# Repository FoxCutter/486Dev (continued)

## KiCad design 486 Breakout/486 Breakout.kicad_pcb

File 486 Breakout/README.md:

# 486 Breakout Board

## SMD parts

The decoupling capacitors for the CPU are made with surface mount parts. This is done because the gap the socket provides between board and CPU is fairly limited, and while Through-Hole parts can be used, they might not have enough clearance. Now these are using 0805/2012 size resistors, and are fairly spread out so there should be enough room even if you've never worked with surface mount parts before.

The capacitors themselves are 1uF (marked as 105), and are fairly inexpensive.

## 7400 ICs

The pair of 7400 NAND gate ICs provide the logic for generating the _BHE#_, _BHL#_, _A1_ and _A0_ and can be left off the board if you do not need or would rather generate those signals yourself.

## CPU Socket

The components on the board and spaced such that a standard ZIF socket should fit correctly. This is not a guarantee, but it should work.

Otherwise, a 17x17 PGA socket (168 or 169 pin) should be used.

## _DP0_-_DP3_

These are the data parity lines for each byte in the data bus. The spec sheet advises that if you are not using them to pull them high. This is what the **J2** jumper block is for.

These lines have no effect other then on the output of the _PCHK#_ pin.

## _RDY#_ and _BRDY#_ jumpers

Jumper block **J10** exists as a way to set the _RDY#_ and _BRDY#_ pins if you don't plan to dynamically set them. The recommended configuration is to pull _RDY#_ low, to indicate that the normal data bus access as complete, and _BRDY#_ to high to disable burst access.

Both High and Low will go through a pull-up resistor, so can be overridden by other parts of the system.

## _IGNNE#_, _KEN#_ and _A20M#_ jumpers

Jumper block **J6** allows you to force any of these three lines to low, as all three are pulled high on the board. _IGNNE#_ is ignored if the NE bit is set in CR0 (which you should do), and the _A20M#_ is the state of the A20 Line mask, and is not very useful unless you are making an IBM PC compatible system.

NOTE: This jumper is the only place where the _A20M#_ line is exposed on the breakout board.

The _KEN#_ line indicates the cachability of the current cycle. And probably isn't worth asserting the line to ground.

## Other Versions of the 486

The breakout board is built around the 486-DX that I own, it should be usable with a later version of the DX chip. Though in that case some of the previously not connected pins will now be connected.

Make sure you cross reference the extra pins against the correct data-sheet for your CPU. I'm hardly an expert and the advice below could turn out to be wrong.

### 486-SX

The original version of the 486SX has a slightly different pin arrangement, and while it should work if you are careful, I wouldn't recommend it. There should be no risk of damaging the CPU, but it might not function as expected.

### Later version of the 486-DX

Later version of the DX add a few new pins, _SRESET_, _SMI#_, _SMIACT#_, _STPCLK#_ and _UP#_. While these have built in pull up/down resisters, if the cpu you are working on has them, it would be best to pull _SRESET_ low, and _SMI#_, _STPCLK#_ and _UP#_ high.

### 486-DX2 And 486-SX2

The biggest change for the DX2 is that the internal clock speed is doubled. It doesn't seem to add any additional pins outside of what was already added above.

The SX2 brought the pins in line with the DX2, so should be fully compatible.

### 486-DX4

The DX4 adds the ability to control the clock multiplier using the **CLKMUL** pin durring a reset. So you need to make sure that the pin is properly pulled up/down depending on how you want to use the multiplier. 

In addititon, the DX4 is a 3 volt CPU.

### 3 Volt CPU

This is probably the most challenging chip to work with, as it runs at 3.3 volts and not 5 volts. It can support 5v logic, but extra steps are needed to provide a 5 volt reference input to the _J1_ pin on the cpu.

Please double check the data sheet before doing this, to make sure things work the way you will want them to!

If you are using the 3.3 volt cpu with 5 volt logic, you must cut jumper **JP1** on the back of the board, and attach a 5 volt input to **TP1**. Failing to do this could cause undefined results.

### Test Port

The test port is available on some DX models, and appears to be on all DX3 and DX4 chips. This adds the _TCK_, _TDI_, _TMS_ and _TDO_ pins. The test port pins are allowed to be unconnected on some versions of the DX and DX2, but it's probably wise to pull the input lines (_TCK_, _TDI_ and _TMS_) high unless you plan on using it.

### Write-Back Enhanced

The Write-Back Enhanced version of the DX2 and DX4 add the _INV_, _HITM#_, _CHACH#_ and _WB-WT#_ pins. The _INV_ pin should be pulled high, while the _FLUSH#_ pin should be pulled low.

### Can I use the 486 Symbol/Footprint in my own projects?

Of course, they are standard Kicad Symbols and Footprint, and you can ues them without credit. I tried to make them as generic as possible for all PGA versions of the DX and majority of SX cpus (the same issues with the SX from above apply). You would need to adjust and add some pins for the QFP versions.

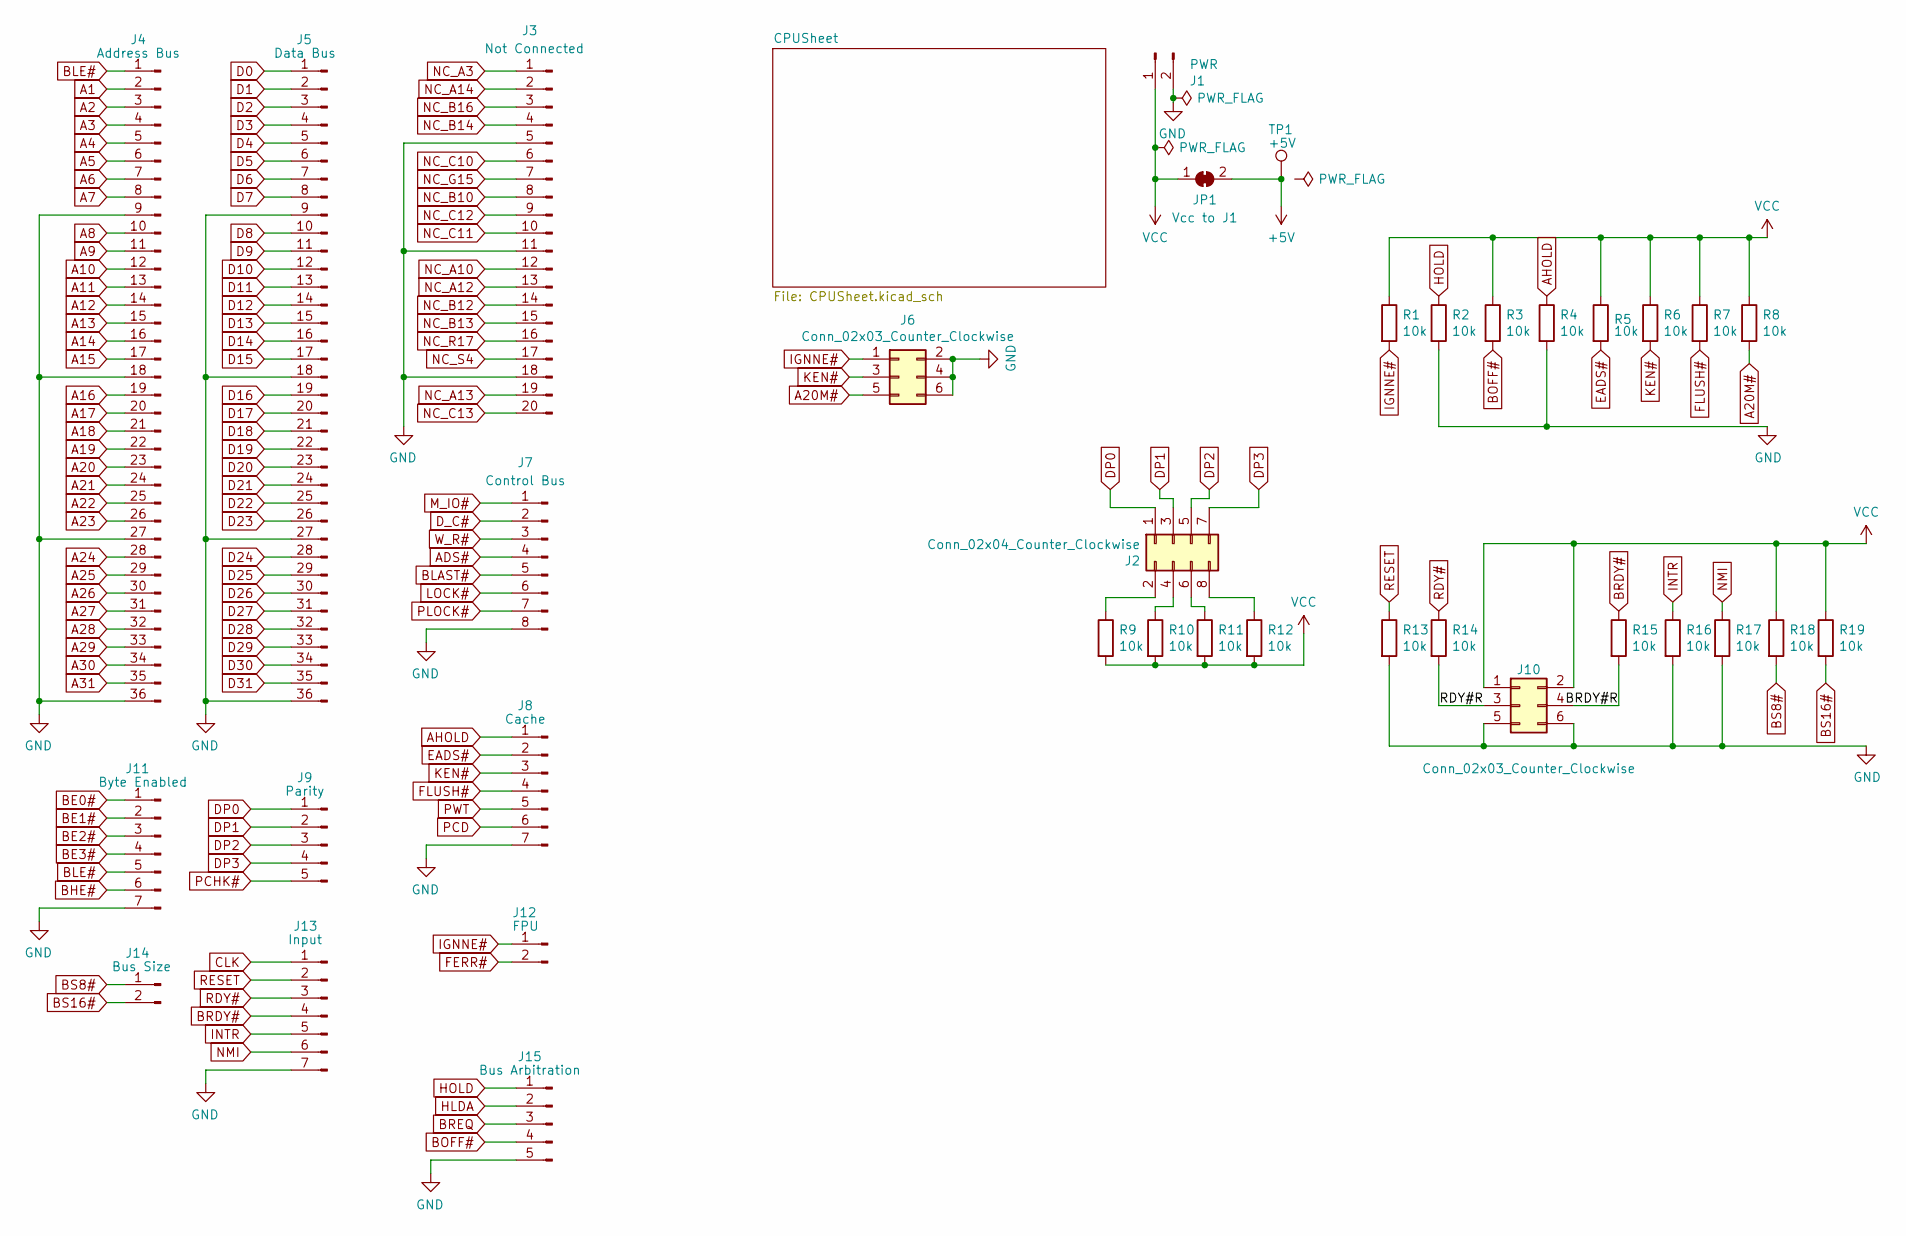
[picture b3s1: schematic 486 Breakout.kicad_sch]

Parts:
J1: PWR; PinHeader_1x02_P2.54mm_Vertical
J2: Conn_02x04_Counter_Clockwise; PinHeader_2x04_P2.54mm_Vertical
J3: Not Connected; PinHeader_1x20_P2.54mm_Vertical
J4: Address Bus; PinHeader_1x36_P2.54mm_Vertical
J5: Data Bus; PinHeader_1x36_P2.54mm_Vertical
J6, J10: Conn_02x03_Counter_Clockwise; PinHeader_2x03_P2.54mm_Vertical
J7: Control Bus; PinHeader_1x08_P2.54mm_Vertical
J8: Cache; PinHeader_1x07_P2.54mm_Vertical
J9: Parity; PinHeader_1x05_P2.54mm_Vertical
J11: Byte Enabled; PinHeader_1x07_P2.54mm_Vertical
J12: FPU; PinHeader_1x02_P2.54mm_Vertical
J13: Input; PinHeader_1x07_P2.54mm_Vertical
J14: Bus Size; PinHeader_1x02_P2.54mm_Vertical
J15: Bus Arbitration; PinHeader_1x05_P2.54mm_Vertical
JP1: Vcc to J1; SolderJumper-2_P1.3mm_Bridged_Pad1.0x1.5mm
R1, R2, R3, R4, R5, R6, R7, R8, R9, R10, R11, R12, R13, R14, R15, R16, R17, R18, R19: 10k; R_Axial_DIN0204_L3.6mm_D1.6mm_P7.62mm_Horizontal
TP1: +5V; TestPoint_Pad_2.0x2.0mm

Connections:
+5V: JP1.2 (B), TP1.1; also elsewhere on the board
/BRDY#R: J10.4, R15.2
/RDY#R: J10.3, R14.2
A1: J4.2; also elsewhere on the board
A2: J4.3; also elsewhere on the board
A3: J4.4; also elsewhere on the board
A4: J4.5; also elsewhere on the board
A5: J4.6; also elsewhere on the board
A6: J4.7; also elsewhere on the board
A7: J4.8; also elsewhere on the board
A8: J4.10; also elsewhere on the board
A9: J4.11; also elsewhere on the board
A10: J4.12; also elsewhere on the board
A11: J4.13; also elsewhere on the board
A12: J4.14; also elsewhere on the board
A13: J4.15; also elsewhere on the board
A14: J4.16; also elsewhere on the board
A15: J4.17; also elsewhere on the board
A16: J4.19; also elsewhere on the board
A17: J4.20; also elsewhere on the board
A18: J4.21; also elsewhere on the board
A19: J4.22; also elsewhere on the board
A20: J4.23; also elsewhere on the board
A20M#: J6.5, R8.2; also elsewhere on the board
A21: J4.24; also elsewhere on the board
A22: J4.25; also elsewhere on the board
A23: J4.26; also elsewhere on the board
A24: J4.28; also elsewhere on the board
A25: J4.29; also elsewhere on the board
A26: J4.30; also elsewhere on the board
A27: J4.31; also elsewhere on the board
A28: J4.32; also elsewhere on the board
A29: J4.33; also elsewhere on the board
A30: J4.34; also elsewhere on the board
A31: J4.35; also elsewhere on the board
ADS#: J7.4; also elsewhere on the board
AHOLD: J8.1, R4.1; also elsewhere on the board
BE0#: J11.1; also elsewhere on the board
BE1#: J11.2; also elsewhere on the board
BE2#: J11.3; also elsewhere on the board
BE3#: J11.4; also elsewhere on the board
BHE#: J11.6; also elsewhere on the board
BLAST#: J7.5; also elsewhere on the board
BLE#: J4.1, J11.5; also elsewhere on the board
BOFF#: J15.4, R3.2; also elsewhere on the board
BRDY#: J13.4, R15.1; also elsewhere on the board
BREQ: J15.3; also elsewhere on the board
BS8#: J14.1, R18.2; also elsewhere on the board
BS16#: J14.2, R19.2; also elsewhere on the board
CLK: J13.1; also elsewhere on the board
D0: J5.1; also elsewhere on the board
D1: J5.2; also elsewhere on the board
D2: J5.3; also elsewhere on the board
D3: J5.4; also elsewhere on the board
D4: J5.5; also elsewhere on the board
D5: J5.6; also elsewhere on the board
D6: J5.7; also elsewhere on the board
D7: J5.8; also elsewhere on the board
D8: J5.10; also elsewhere on the board
D9: J5.11; also elsewhere on the board
D10: J5.12; also elsewhere on the board
D11: J5.13; also elsewhere on the board
D12: J5.14; also elsewhere on the board
D13: J5.15; also elsewhere on the board
D14: J5.16; also elsewhere on the board
D15: J5.17; also elsewhere on the board
D16: J5.19; also elsewhere on the board
D17: J5.20; also elsewhere on the board
D18: J5.21; also elsewhere on the board
D19: J5.22; also elsewhere on the board
D20: J5.23; also elsewhere on the board
D21: J5.24; also elsewhere on the board
D22: J5.25; also elsewhere on the board
D23: J5.26; also elsewhere on the board
D24: J5.28; also elsewhere on the board
D25: J5.29; also elsewhere on the board
D26: J5.30; also elsewhere on the board
D27: J5.31; also elsewhere on the board
D28: J5.32; also elsewhere on the board
D29: J5.33; also elsewhere on the board
D30: J5.34; also elsewhere on the board
D31: J5.35; also elsewhere on the board
DP0: J2.1, J9.1; also elsewhere on the board
DP1: J2.3, J9.2; also elsewhere on the board
DP2: J2.5, J9.3; also elsewhere on the board
DP3: J2.7, J9.4; also elsewhere on the board
D_C#: J7.2; also elsewhere on the board
EADS#: J8.2, R5.2; also elsewhere on the board
FERR#: J12.2; also elsewhere on the board
FLUSH#: J8.4, R7.2; also elsewhere on the board
GND: J1.2, J3.5, J3.11, J3.18, J4.9, J4.18, J4.27, J4.36, J5.9, J5.18, J5.27, J5.36, J6.2, J6.4, J6.6, J7.8, J8.7, J10.5, J10.6, J11.7, J13.7, J15.5, R2.2, R4.2, R13.2, R16.2, R17.2; also elsewhere on the board
HLDA: J15.2; also elsewhere on the board
HOLD: J15.1, R2.1; also elsewhere on the board
IGNNE#: J6.1, J12.1, R1.2; also elsewhere on the board
INTR: J13.5, R16.1; also elsewhere on the board
KEN#: J6.3, J8.3, R6.2; also elsewhere on the board
LOCK#: J7.6; also elsewhere on the board
M_IO#: J7.1; also elsewhere on the board
NC_A3: J3.1; also elsewhere on the board
NC_A10: J3.12; also elsewhere on the board
NC_A12: J3.13; also elsewhere on the board
NC_A13: J3.19; also elsewhere on the board
NC_A14: J3.2; also elsewhere on the board
NC_B10: J3.8; also elsewhere on the board
NC_B12: J3.14; also elsewhere on the board
NC_B13: J3.15; also elsewhere on the board
NC_B14: J3.4; also elsewhere on the board
NC_B16: J3.3; also elsewhere on the board
NC_C10: J3.6; also elsewhere on the board
NC_C11: J3.10; also elsewhere on the board
NC_C12: J3.9; also elsewhere on the board
NC_C13: J3.20; also elsewhere on the board
NC_G15: J3.7; also elsewhere on the board
NC_R17: J3.16; also elsewhere on the board
NC_S4: J3.17; also elsewhere on the board
NMI: J13.6, R17.1; also elsewhere on the board
unnamed: J2.2, R9.1
unnamed: J2.4, R10.1
unnamed: J2.6, R11.1
unnamed: J2.8, R12.1
PCD: J8.6; also elsewhere on the board
PCHK#: J9.5; also elsewhere on the board
PLOCK#: J7.7; also elsewhere on the board
PWT: J8.5; also elsewhere on the board
RDY#: J13.3, R14.1; also elsewhere on the board
RESET: J13.2, R13.1; also elsewhere on the board
VCC: J1.1, J10.1, J10.2, JP1.1 (A), R1.1, R3.1, R5.1, R6.1, R7.1, R8.1, R9.2, R10.2, R11.2, R12.2, R18.1, R19.1; also elsewhere on the board
W_R#: J7.3; also elsewhere on the board

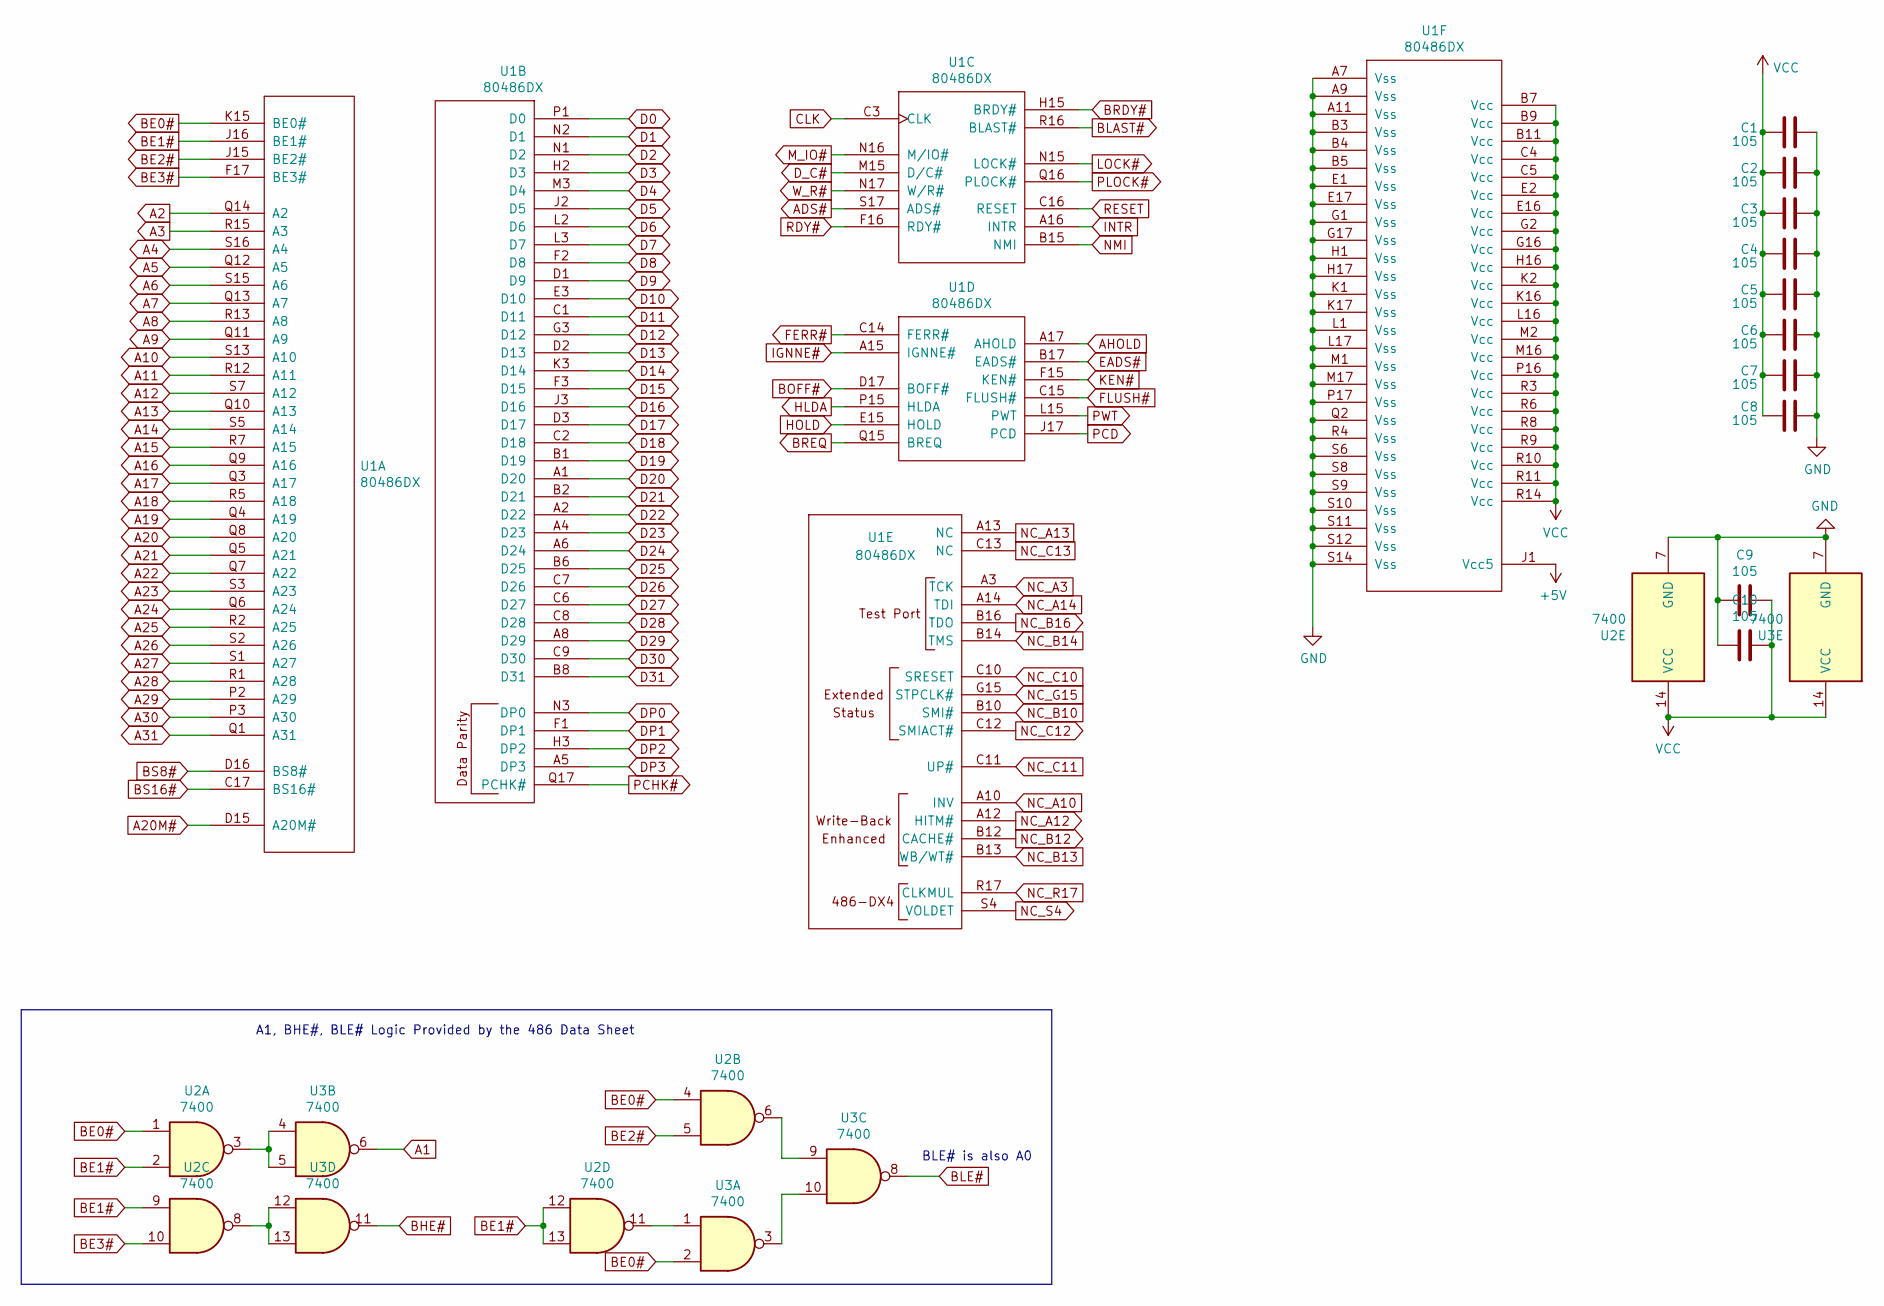
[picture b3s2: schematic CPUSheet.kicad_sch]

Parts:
C1, C2, C3, C4, C5, C6, C7, C8: 105; C_0805_2012Metric_Pad1.18x1.45mm_HandSolder
C9, C10: 105; C_Disc_D3.4mm_W2.1mm_P2.50mm
U1: 80486DX; PGA169
U2, U3: 7400; DIP-14_W7.62mm

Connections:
+5V: U1.J1 (Vcc5); also elsewhere on the board
A1: U3.6; also elsewhere on the board
A2: U1.Q14 (A2); also elsewhere on the board
A3: U1.R15 (A3); also elsewhere on the board
A4: U1.S16 (A4); also elsewhere on the board
A5: U1.Q12 (A5); also elsewhere on the board
A6: U1.S15 (A6); also elsewhere on the board
A7: U1.Q13 (A7); also elsewhere on the board
A8: U1.R13 (A8); also elsewhere on the board
A9: U1.Q11 (A9); also elsewhere on the board
A10: U1.S13 (A10); also elsewhere on the board
A11: U1.R12 (A11); also elsewhere on the board
A12: U1.S7 (A12); also elsewhere on the board
A13: U1.Q10 (A13); also elsewhere on the board
A14: U1.S5 (A14); also elsewhere on the board
A15: U1.R7 (A15); also elsewhere on the board
A16: U1.Q9 (A16); also elsewhere on the board
A17: U1.Q3 (A17); also elsewhere on the board
A18: U1.R5 (A18); also elsewhere on the board
A19: U1.Q4 (A19); also elsewhere on the board
A20: U1.Q8 (A20); also elsewhere on the board
A20M#: U1.D15 (A20M#); also elsewhere on the board
A21: U1.Q5 (A21); also elsewhere on the board
A22: U1.Q7 (A22); also elsewhere on the board
A23: U1.S3 (A23); also elsewhere on the board
A24: U1.Q6 (A24); also elsewhere on the board
A25: U1.R2 (A25); also elsewhere on the board
A26: U1.S2 (A26); also elsewhere on the board
A27: U1.S1 (A27); also elsewhere on the board
A28: U1.R1 (A28); also elsewhere on the board
A29: U1.P2 (A29); also elsewhere on the board
A30: U1.P3 (A30); also elsewhere on the board
A31: U1.Q1 (A31); also elsewhere on the board
ADS#: U1.S17 (ADS#); also elsewhere on the board
AHOLD: U1.A17 (AHOLD); also elsewhere on the board
BE0#: U1.K15 (BE0#), U2.1, U2.4, U3.2; also elsewhere on the board
BE1#: U1.J16 (BE1#), U2.2, U2.9, U2.12, U2.13; also elsewhere on the board
BE2#: U1.J15 (BE2#), U2.5; also elsewhere on the board
BE3#: U1.F17 (BE3#), U2.10; also elsewhere on the board
BHE#: U3.11; also elsewhere on the board
BLAST#: U1.R16 (BLAST#); also elsewhere on the board
BLE#: U3.8; also elsewhere on the board
BOFF#: U1.D17 (BOFF#); also elsewhere on the board
BRDY#: U1.H15 (BRDY#); also elsewhere on the board
BREQ: U1.Q15 (BREQ); also elsewhere on the board
BS8#: U1.D16 (BS8#); also elsewhere on the board
BS16#: U1.C17 (BS16#); also elsewhere on the board
CLK: U1.C3 (CLK); also elsewhere on the board
D0: U1.P1 (D0); also elsewhere on the board
D1: U1.N2 (D1); also elsewhere on the board
D2: U1.N1 (D2); also elsewhere on the board
D3: U1.H2 (D3); also elsewhere on the board
D4: U1.M3 (D4); also elsewhere on the board
D5: U1.J2 (D5); also elsewhere on the board
D6: U1.L2 (D6); also elsewhere on the board
D7: U1.L3 (D7); also elsewhere on the board
D8: U1.F2 (D8); also elsewhere on the board
D9: U1.D1 (D9); also elsewhere on the board
D10: U1.E3 (D10); also elsewhere on the board
D11: U1.C1 (D11); also elsewhere on the board
D12: U1.G3 (D12); also elsewhere on the board
D13: U1.D2 (D13); also elsewhere on the board
D14: U1.K3 (D14); also elsewhere on the board
D15: U1.F3 (D15); also elsewhere on the board
D16: U1.J3 (D16); also elsewhere on the board
D17: U1.D3 (D17); also elsewhere on the board
D18: U1.C2 (D18); also elsewhere on the board
D19: U1.B1 (D19); also elsewhere on the board
D20: U1.A1 (D20); also elsewhere on the board
D21: U1.B2 (D21); also elsewhere on the board
D22: U1.A2 (D22); also elsewhere on the board
D23: U1.A4 (D23); also elsewhere on the board
D24: U1.A6 (D24); also elsewhere on the board
D25: U1.B6 (D25); also elsewhere on the board
D26: U1.C7 (D26); also elsewhere on the board
D27: U1.C6 (D27); also elsewhere on the board
D28: U1.C8 (D28); also elsewhere on the board
D29: U1.A8 (D29); also elsewhere on the board
D30: U1.C9 (D30); also elsewhere on the board
D31: U1.B8 (D31); also elsewhere on the board
DP0: U1.N3 (DP0); also elsewhere on the board
DP1: U1.F1 (DP1); also elsewhere on the board
DP2: U1.H3 (DP2); also elsewhere on the board
DP3: U1.A5 (DP3); also elsewhere on the board
D_C#: U1.M15 (D/C#); also elsewhere on the board
EADS#: U1.B17 (EADS#); also elsewhere on the board
FERR#: U1.C14 (FERR#); also elsewhere on the board
FLUSH#: U1.C15 (FLUSH#); also elsewhere on the board
GND: C1.1, C2.1, C3.1, C4.1, C5.1, C6.1, C7.1, C8.1, C9.2, C10.2, U1.A7 (Vss), U1.A9 (Vss), U1.A11 (Vss), U1.B3 (Vss), U1.B4 (Vss), U1.B5 (Vss), U1.E1 (Vss), U1.E17 (Vss), U1.G1 (Vss), U1.G17 (Vss), U1.H1 (Vss), U1.H17 (Vss), U1.K1 (Vss), U1.K17 (Vss), U1.L1 (Vss), U1.L17 (Vss), U1.M1 (Vss), U1.M17 (Vss), U1.P17 (Vss), U1.Q2 (Vss), U1.R4 (Vss), U1.S6 (Vss), U1.S8 (Vss), U1.S9 (Vss), U1.S10 (Vss), U1.S11 (Vss), U1.S12 (Vss), U1.S14 (Vss), U2.7 (GND), U3.7 (GND); also elsewhere on the board
HLDA: U1.P15 (HLDA); also elsewhere on the board
HOLD: U1.E15 (HOLD); also elsewhere on the board
IGNNE#: U1.A15 (IGNNE#); also elsewhere on the board
INTR: U1.A16 (INTR); also elsewhere on the board
KEN#: U1.F15 (KEN#); also elsewhere on the board
LOCK#: U1.N15 (LOCK#); also elsewhere on the board
M_IO#: U1.N16 (M/IO#); also elsewhere on the board
NC_A3: U1.A3 (TCK); also elsewhere on the board
NC_A10: U1.A10 (INV); also elsewhere on the board
NC_A12: U1.A12 (HITM#); also elsewhere on the board
NC_A13: U1.A13 (NC); also elsewhere on the board
NC_A14: U1.A14 (TDI); also elsewhere on the board
NC_B10: U1.B10 (SMI#); also elsewhere on the board
NC_B12: U1.B12 (CACHE#); also elsewhere on the board
NC_B13: U1.B13 (WB/WT#); also elsewhere on the board
NC_B14: U1.B14 (TMS); also elsewhere on the board
NC_B16: U1.B16 (TDO); also elsewhere on the board
NC_C10: U1.C10 (SRESET); also elsewhere on the board
NC_C11: U1.C11 (UP#); also elsewhere on the board
NC_C12: U1.C12 (SMIACT#); also elsewhere on the board
NC_C13: U1.C13 (NC); also elsewhere on the board
NC_G15: U1.G15 (STPCLK#); also elsewhere on the board
NC_R17: U1.R17 (CLKMUL); also elsewhere on the board
NC_S4: U1.S4 (VOLDET); also elsewhere on the board
NMI: U1.B15 (NMI); also elsewhere on the board
unnamed: U2.3, U3.4, U3.5
unnamed: U2.6, U3.9
unnamed: U2.8, U3.12, U3.13
unnamed: U2.11, U3.1
unnamed: U3.3, U3.10
PCD: U1.J17 (PCD); also elsewhere on the board
PCHK#: U1.Q17 (PCHK#); also elsewhere on the board
PLOCK#: U1.Q16 (PLOCK#); also elsewhere on the board
PWT: U1.L15 (PWT); also elsewhere on the board
RDY#: U1.F16 (RDY#); also elsewhere on the board
RESET: U1.C16 (RESET); also elsewhere on the board
VCC: C1.2, C2.2, C3.2, C4.2, C5.2, C6.2, C7.2, C8.2, C9.1, C10.1, U1.B7 (Vcc), U1.B9 (Vcc), U1.B11 (Vcc), U1.C4 (Vcc), U1.C5 (Vcc), U1.E2 (Vcc), U1.E16 (Vcc), U1.G2 (Vcc), U1.G16 (Vcc), U1.H16 (Vcc), U1.K2 (Vcc), U1.K16 (Vcc), U1.L16 (Vcc), U1.M2 (Vcc), U1.M16 (Vcc), U1.P16 (Vcc), U1.R3 (Vcc), U1.R6 (Vcc), U1.R8 (Vcc), U1.R9 (Vcc), U1.R10 (Vcc), U1.R11 (Vcc), U1.R14 (Vcc), U2.14 (VCC), U3.14 (VCC); also elsewhere on the board
W_R#: U1.N17 (W/R#); also elsewhere on the board

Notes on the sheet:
A1, BHE#, BLE# Logic Provided by the 486 Data Sheet
BLE# is also A0

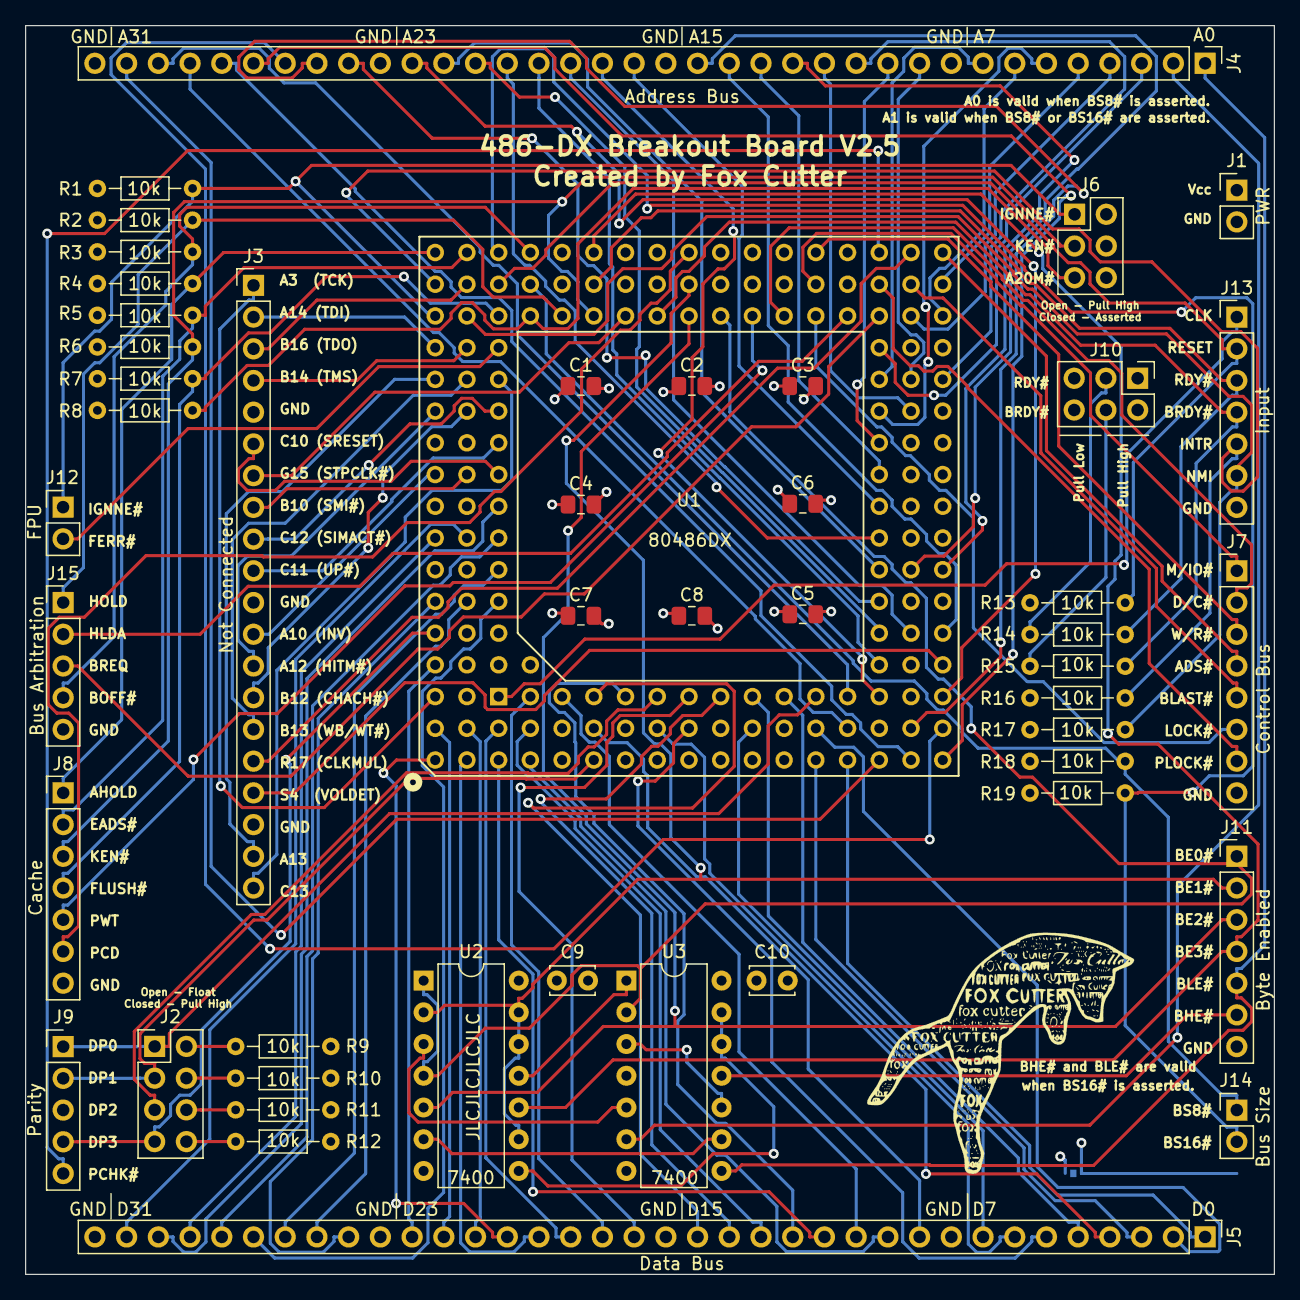
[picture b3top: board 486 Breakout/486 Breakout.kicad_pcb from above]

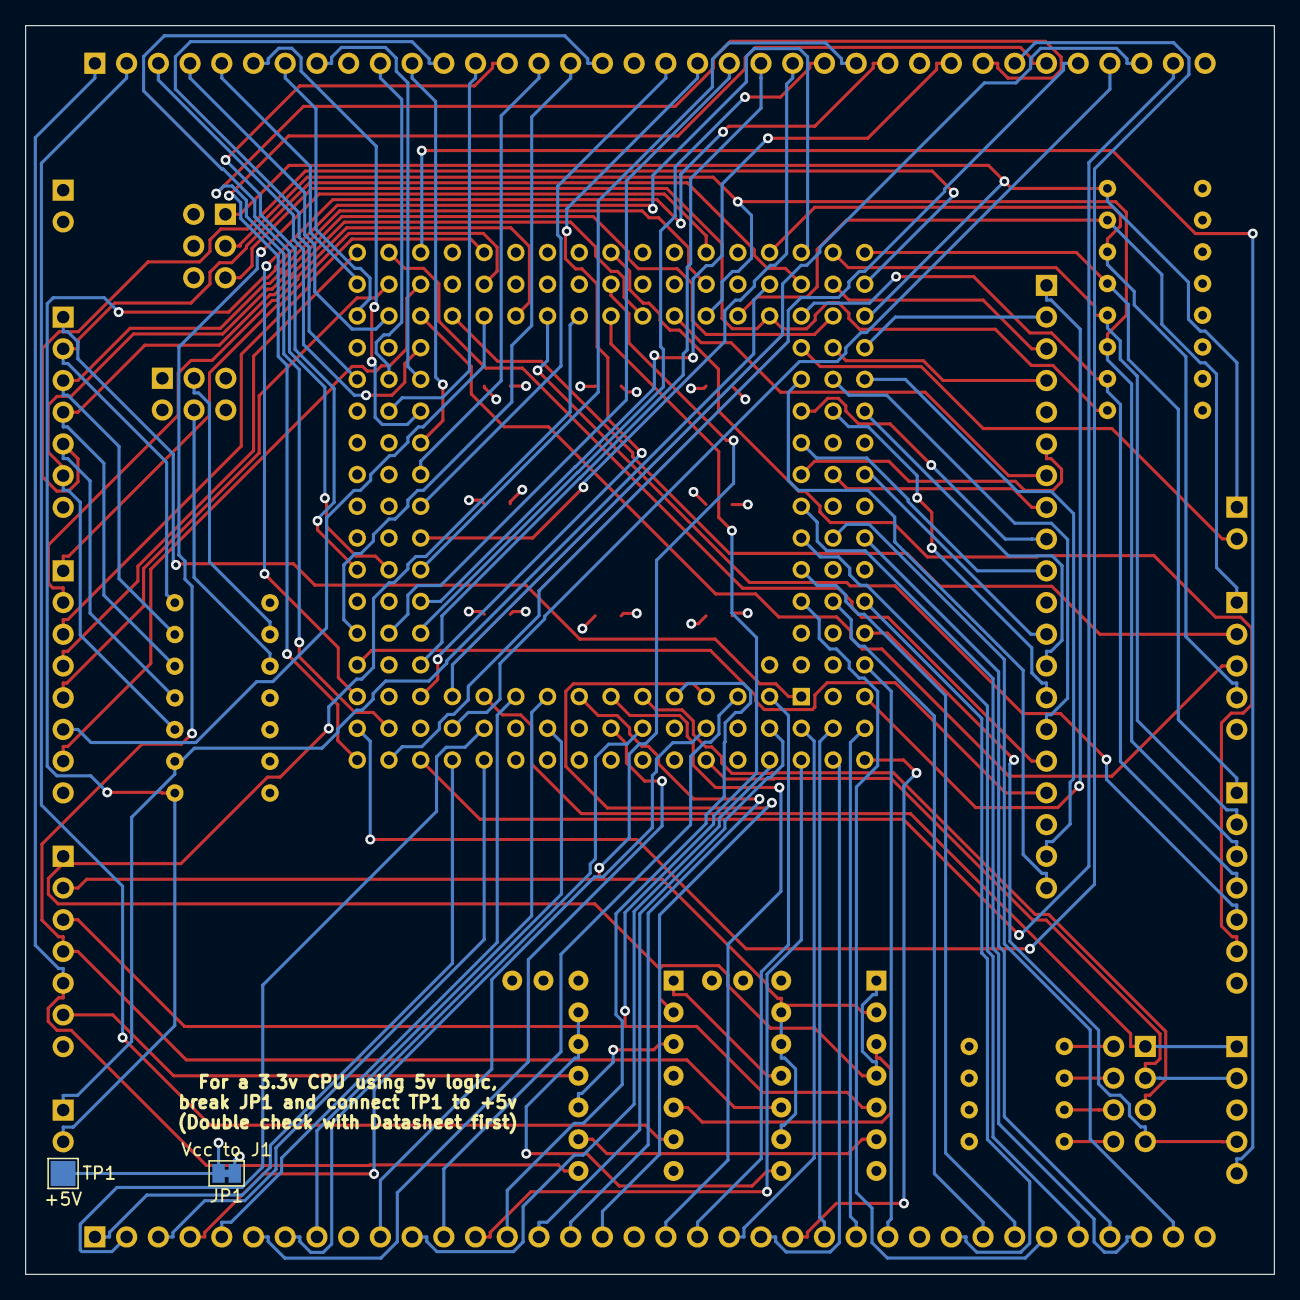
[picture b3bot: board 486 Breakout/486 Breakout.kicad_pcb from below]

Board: 4 copper layers, 100.0 x 100.0 mm, 49 parts (2 on the bottom side), 133 nets.
